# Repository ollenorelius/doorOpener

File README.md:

## doorOpener

This is the PCB for my BLE door opener, based on a nRF52831 microcontroller

### Version 1.1
- Fixed 3v3 not being connected to micro
- Fixed HV high side switch mosfet being the wrong way around (damn body diode!)
- Fixed error in footprint of AP1609

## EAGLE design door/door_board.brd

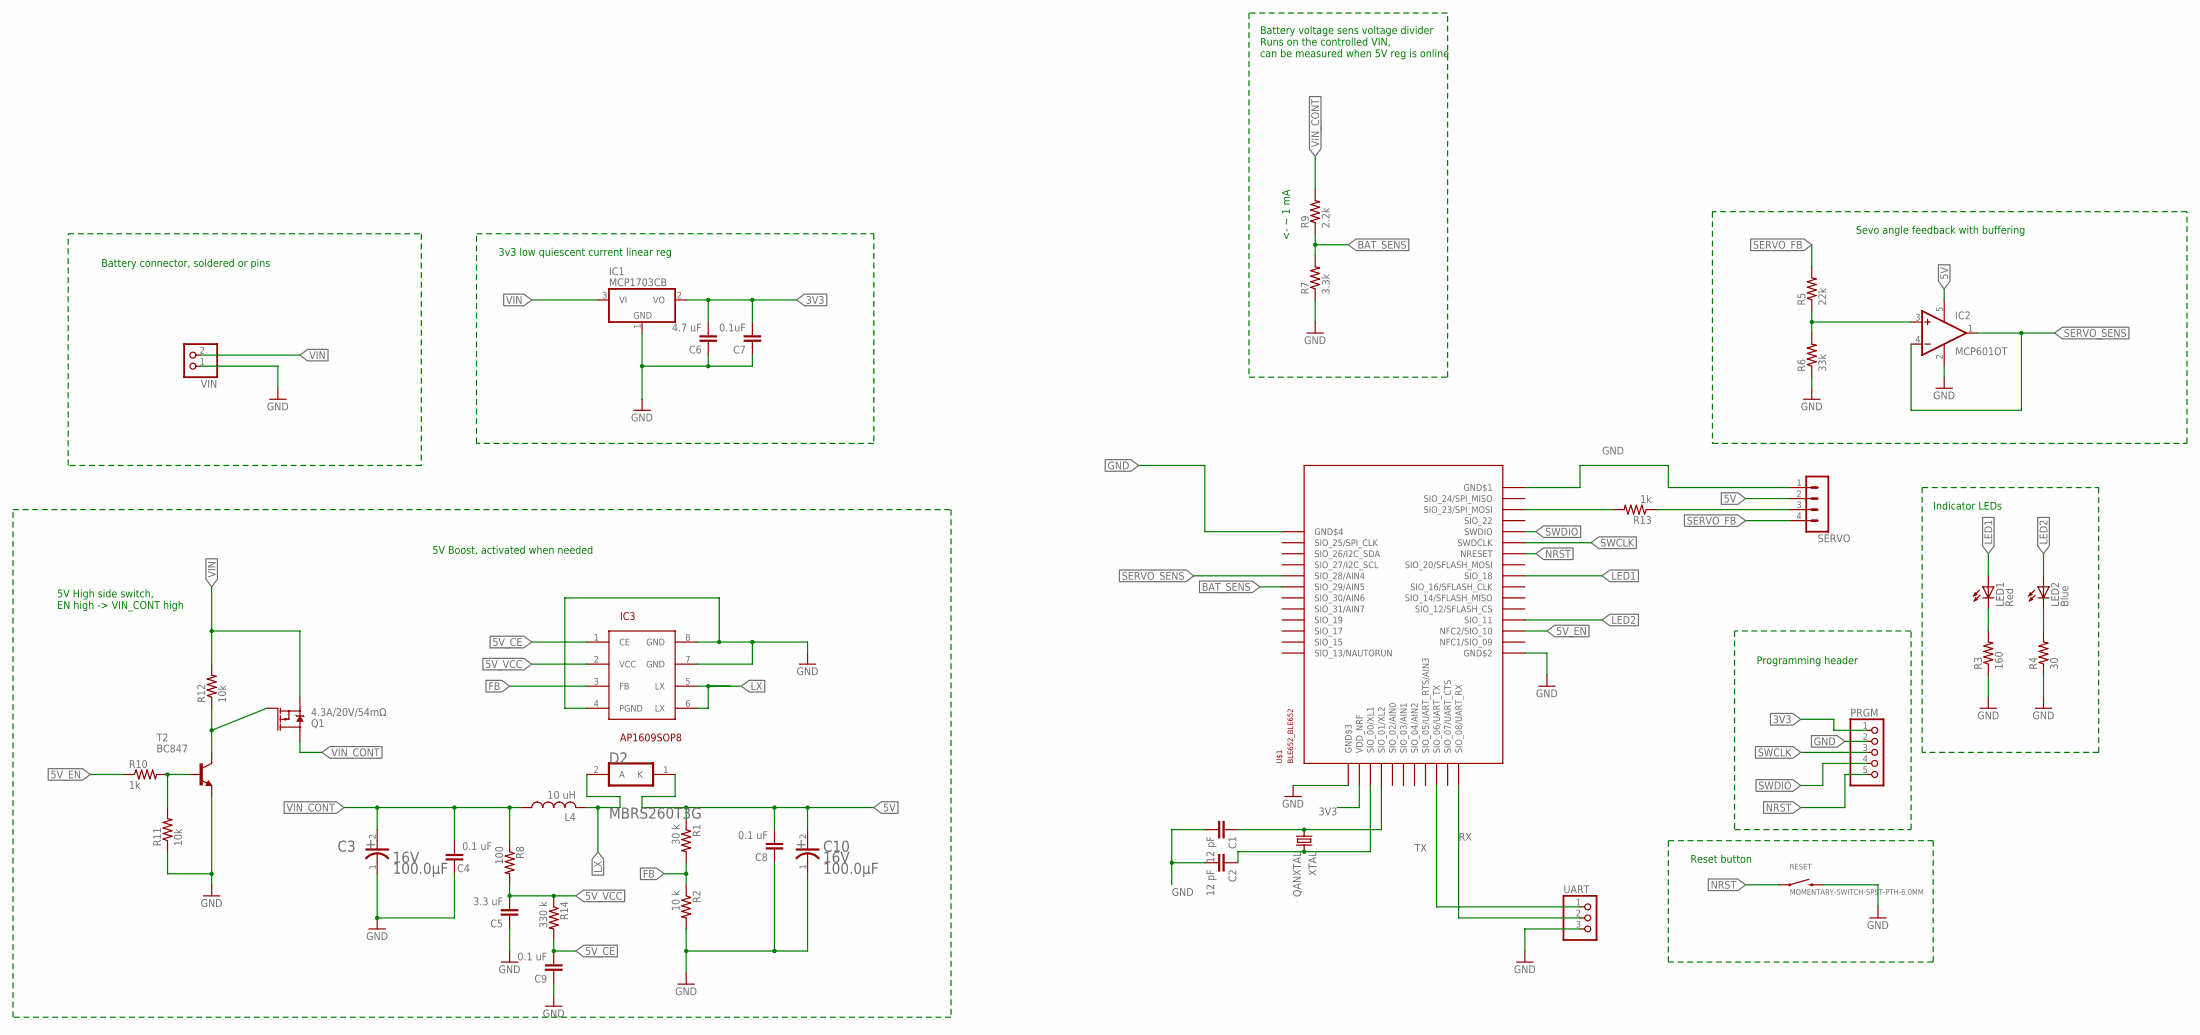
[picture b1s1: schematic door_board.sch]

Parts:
C1, C2: 12 pF; C0603
C3, C10: PANASONIC_EEE-FK1C101PPANASONIC_EEE-FK1C101P_0_0; PANASONIC_EEE-FK1C101P_0
C4, C8, C9: 0.1 uF; C0805
C5: 3.3 uF; C0805
C6: 4.7 uF; C0805
C7: 0.1uF; C0805
D2: ON_SEMICONDUCTOR_MBRS260T3GON_SEMICONDUCTOR_MBRS2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; ON_SEMICONDUCTOR_MBRS260T3G_0
IC1: MCP1703CB; SOT23
IC2: MCP601OT; SOT23-5
IC3: AP1609SOP8; SOIC127P600X175-8
L4: 10 uH; SMT
LED1: Red; CHIP-LED0805
LED2: Blue; CHIP-LED0805
PRGM: PINHD-1X5; 1X05
Q1: 4.3A/20V/54mΩ; SOT23-3
R1: 30 k; M0805
R2: 10 k; M0805
R3: 160; M0805
R4: 30; M0805
R5: 22k; M0805
R6: 33k; M0805
R7: 3.3k; M0805
R8: 100; M0805
R9: 2.2k; M0805
R10, R13: 1k; M0805
R11, R12: 10k; M0805
R14: 330 k; M0805
RESET: MOMENTARY-SWITCH-SPST-PTH-6.0MM; TACTILE_SWITCH_PTH_6.0MM
SERVO: MA04-1
T2: BC847; SOT23
U$1: BLE652_BLE652; BLE652_BL652
UART: PINHD-1X3; 1X03
VIN: PINHD-1X2; 1X02
XTAL: QANXTAL; QANTEKXTAL

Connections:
3V3: C6.2, C7.2, IC1.2 (VO), PRGM.1, U$1.P$26 (VDD_NRF)
5V: C8.2, C10.2 (ANODE), D2.1 (K), IC2.5 (V+), R1.1, SERVO.2
5V_CE: C9.2, IC3.1 (CE), R14.2
5V_EN: R10.1, U$1.P$14 (NFC2/SIO_10)
5V_VCC: C5.2, IC3.2 (VCC), R8.2, R14.1
ADFSGSDFH: IC2.3 (+IN), R5.1, R6.2
BAT_SENS: R7.2, R9.1, U$1.P$34 (SIO_29/AIN5)
FB: IC3.3 (FB), R1.2, R2.1
GND: C1.2, C2.2, C3.1 (CATHODE), C4.1, C5.1, C6.1, C7.1, C8.1, C9.1, C10.1 (CATHODE), IC1.1 (GND), IC2.2 (V-), IC3.4 (PGND), IC3.7 (GND), IC3.8 (GND), PRGM.2, R2.2, R3.1, R4.1, R6.1, R7.1, R11.1, RESET.3 (2), SERVO.1, T2.2 (E), U$1.P$1 (GND$1), U$1.P$16 (GND$2), U$1.P$27 (GND$3), U$1.P$39 (GND$4), UART.3, VIN.1
LED1: LED1.A, U$1.P$9 (SIO_18)
LED2: LED2.A, U$1.P$13 (SIO_11)
LX: D2.2 (A), IC3.5 (LX), IC3.6 (LX), L4.P2 (2)
unnamed: C1.1, U$1.P$24 (SIO_01/XL2), XTAL.1
unnamed: C2.1, U$1.P$25 (SIO_00/XL1), XTAL.2
unnamed: R13.1, SERVO.3
unnamed: LED2.C, R4.2
unnamed: LED1.C, R3.2
unnamed: R10.2, R11.2, T2.1 (B)
unnamed: Q1.1 (G), R12.1, T2.3 (C)
unnamed: R13.2, U$1.P$3 (SIO_23/SPI_MOSI)
NRST: PRGM.5, RESET.1, U$1.P$7 (NRESET)
RX: U$1.P$17 (SIO_08/UART_RX), UART.2
SERVO_FB: R5.2, SERVO.4
SERVO_SENS: IC2.1 (OUT), IC2.4 (-IN), U$1.P$35 (SIO_28/AIN4)
SWCLK: PRGM.3, U$1.P$6 (SWDCLK)
SWDIO: PRGM.4, U$1.P$5 (SWDIO)
TX: U$1.P$19 (SIO_06/UART_TX), UART.1
VIN: IC1.3 (VI), Q1.2 (S), R12.2, VIN.2
VIN_CONT: C3.2 (ANODE), C4.2, L4.P1 (1), Q1.3 (D), R8.1, R9.2

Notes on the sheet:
<- ~ 1 mA
Battery voltage sens voltage divider Runs on the controlled VIN, can be measured when 5V reg is online
Sevo angle feedback with buffering
Indicator LEDs
Programming header
5V Boost, activated when needed
3v3 low quiescent current linear reg
Reset button
Battery connector, soldered or pins
5V High side switch, EN high -> VIN_CONT high

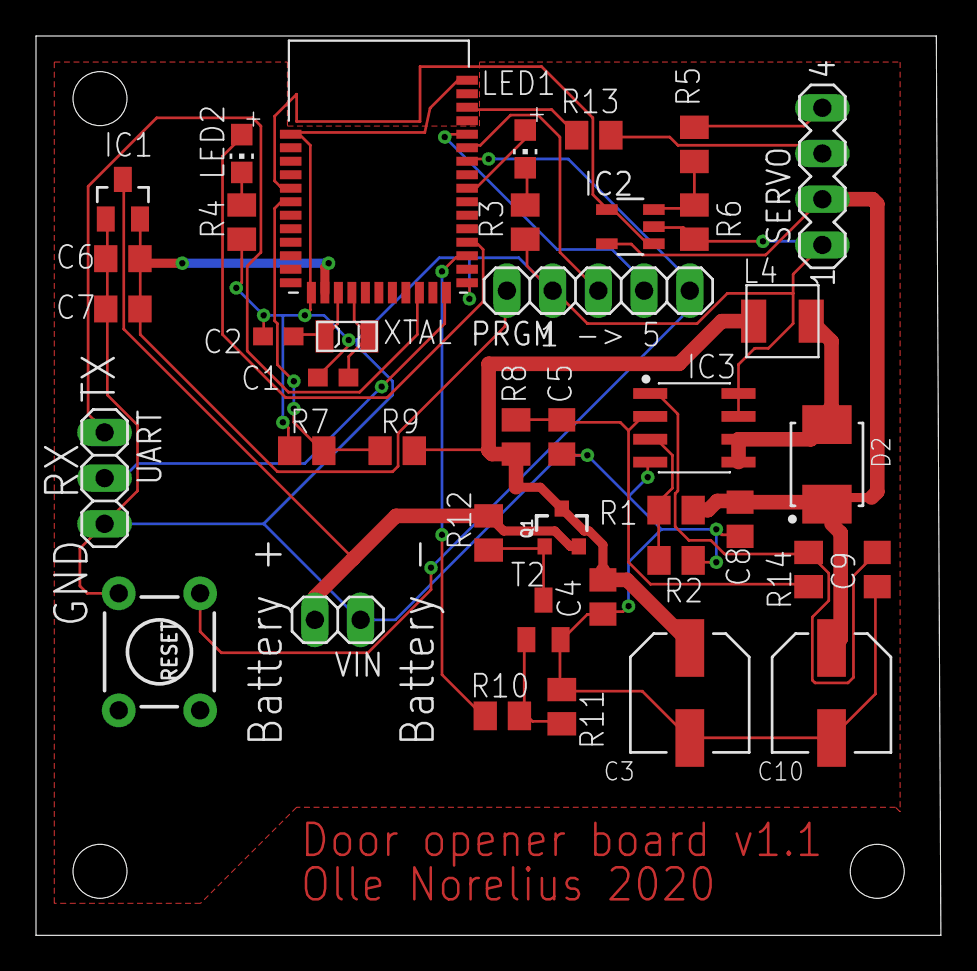
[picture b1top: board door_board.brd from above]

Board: 2 copper layers, 50.3 x 50.0 mm, 40 parts (0 on the bottom side), 29 nets.

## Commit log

2019-03-28 initial PCB commit
2020-03-29 Updated board to version 1.1
    Fixed VCC to nrf
    Flipped HV enable high side mosfet
    Corrected AP1609 footprint
    Updated board text
2020-03-29 Version text updated
    Forgot this in last commit

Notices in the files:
parts and their libraries:
SparkFun-DiscreteSemi: Licensing: Creative Commons ShareAlike 4.0 International - https://creativecommons.org/licenses/by-sa/4.0
